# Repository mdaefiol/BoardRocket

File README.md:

# BoardRocket
Placa utilizada como computador de bordo para foguetes experimentais (REV-A 06/06/23).

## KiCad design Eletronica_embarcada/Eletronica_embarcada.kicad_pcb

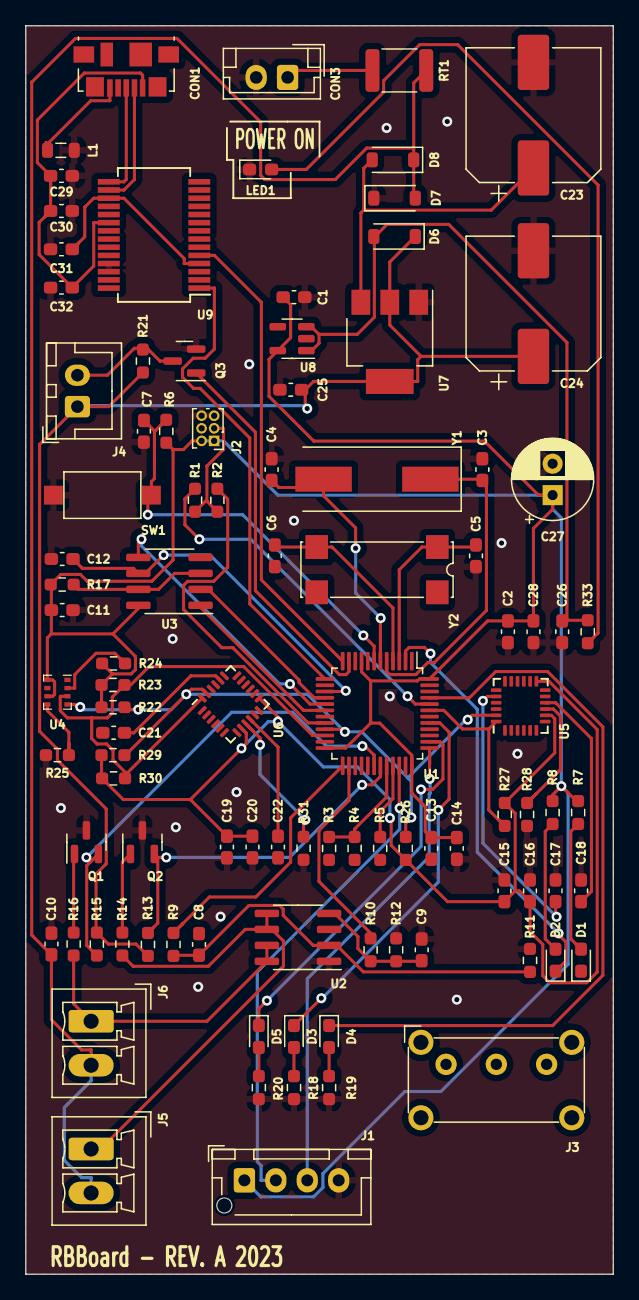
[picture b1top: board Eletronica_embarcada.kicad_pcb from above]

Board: 2 copper layers, 46.7 x 99.3 mm, 98 parts (0 on the bottom side), 65 nets.

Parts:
C1, C2, C7, C8, C9, C25: 100n; C_0603_1608Metric_Pad1.08x0.95mm_HandSolder
C3, C4, C5, C6: 20p; C_0603_1608Metric_Pad1.08x0.95mm_HandSolder
C10, C14: 1u; C_0603_1608Metric_Pad1.08x0.95mm_HandSolder
C11, C26, C28, C32: 100nF; C_0603_1608Metric_Pad1.08x0.95mm_HandSolder
C12: 47pF; C_0603_1608Metric_Pad1.08x0.95mm_HandSolder
C13: 0.1u; C_0603_1608Metric_Pad1.08x0.95mm_HandSolder
C15, C18, C19, C22: 0.1uF; C_0603_1608Metric_Pad1.08x0.95mm_HandSolder
C16, C20: 0.01uF; C_0603_1608Metric_Pad1.08x0.95mm_HandSolder
C17, C21: 2200pF; C_0603_1608Metric_Pad1.08x0.95mm_HandSolder
C23: 470u, 16V; CP_Elec_10x10.5
C24: 1000u,16V; CP_Elec_10x10.5
C27: 220uFx16V; CP_Radial_D6.3mm_P2.50mm
C29: 10nF; C_0603_1608Metric_Pad1.08x0.95mm_HandSolder
C30: 4,7uF; C_0603_1608Metric_Pad1.08x0.95mm_HandSolder
C31: 1uF; C_0603_1608Metric_Pad1.08x0.95mm_HandSolder
CON1: USB_B; USB_Micro-B_Molex_47346-0001
CON3: Bateria min 7V; JST_EH_B2B-EH-A_1x02_P2.50mm_Vertical
D1, D2, D3, D4, D5: LED; LED_0603_1608Metric_Pad1.05x0.95mm_HandSolder
D6, D8: D; D_SOD-123
D7: DSS14U; D_SOD-123
J1: OUT_Bluepill; JST_XH_B4B-XH-AM_1x04_P2.50mm_Vertical
J2: BOOT_JUMPER; PinHeader_2x03_P1.00mm_Vertical
J3: Switch; SW_E-Switch_EG1224_SPDT_Angled
J4: BUZZER; JST_XH_B2B-XH-A_1x02_P2.50mm_Vertical
J5, J6: Screw_Terminal; PhoenixContact_MCV_1,5_2-G-3.5_1x02_P3.50mm_Vertical
L1: BBPY0020; L_0805_2012Metric
LED1: Power ON; LED_0603_1608Metric_Pad1.05x0.95mm_HandSolder
Q1, Q2: MMBT6427-F; SOT-23
Q3: BC817; SOT-23
R1, R2: 100K; R_0603_1608Metric_Pad0.98x0.95mm_HandSolder
R3, R26, R27, R28, R29, R30, R31: 4.7k; R_0603_1608Metric_Pad0.98x0.95mm_HandSolder
R4, R5: 20R; R_0603_1608Metric_Pad0.98x0.95mm_HandSolder
R6, R11, R12, R13, R15: 10k; R_0603_1608Metric_Pad0.98x0.95mm_HandSolder
R7: 510R; R_0603_1608Metric_Pad0.98x0.95mm_HandSolder
R8: 510; R_0603_1608Metric_Pad0.98x0.95mm_HandSolder
R9, R10: 1.5K; R_0603_1608Metric_Pad0.98x0.95mm_HandSolder
R14, R16: 1M; R_0603_1608Metric_Pad0.98x0.95mm_HandSolder
R17: 22k; R_0603_1608Metric_Pad0.98x0.95mm_HandSolder
R18, R19, R20: 330; R_0603_1608Metric_Pad0.98x0.95mm_HandSolder
R21: 1,5k; R_0603_1608Metric_Pad0.98x0.95mm_HandSolder
R22, R23, R24, R25: 10K; R_0603_1608Metric_Pad0.98x0.95mm_HandSolder
R33: 470R; R_0603_1608Metric_Pad0.98x0.95mm_HandSolder
RT1: 300mA - 304N; R_1812_4532Metric
SW1: SW_Push; SW_SPST_CK_RS282G05A3
U1: STM32F103CBT6; LQFP-48_7x7mm_P0.5mm
U2: IRF7101; SOIC-8_3.9x4.9mm_P1.27mm
U3: MB85RS256B; SOIC-8_3.9x4.9mm_P1.27mm
U4: BMP280; Bosch_LGA-8_2x2.5mm_P0.65mm_ClockwisePinNumbering
U5, U6: MPU-6050; InvenSense_QFN-24_4x4mm_P0.5mm
U7: NCP1117-5.0_SOT223; SOT-223-3_TabPin2
U8: TPS7A0533PDBV; SOT-23-5
U9: FT232RL; SSOP-28_5.3x10.2mm_P0.65mm
Y1: 8M; Crystal_SMD_HC49-SD
Y2: 32k; Crystal_SMD_SeikoEpson_MA406-4Pin_11.7x4.0mm

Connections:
0: C1.2, C2.2, C3.2, C4.2, C5.2, C6.2, C7.2, C8.2, C9.2, C10.2, C11.2, C12.2, C13.2, C14.2, C15.2, C16.2, C17.2, C18.2, C19.2, C20.2, C21.2, C22.2, C23.2, C24.2, C25.2, C26.2, C27.2, C28.2, C29.2, C30.2, C31.2, C32.2, CON1.4 (GND), CON3.2 (-), D7.1 (K), J1.4, J2.5, J2.6, L1.1, LED1.1 (K), Q1.3 (E), Q2.3 (E), Q3.2 (E), R11.2, R12.2, R18.1, R19.1, R20.1, R25.2, R28.2, R31.2, SW1.2, U1.8 (VSSA), U1.23 (VSS), U1.35 (VSS), U1.47 (VSS), U2.1 (S1), U2.3 (S2), U3.4 (VSS), U4.1 (GND), U4.7 (GND), U5.1 (CLKIN), U5.11 (FSYNC), U5.18 (GND), U6.1 (CLKIN), U6.11 (FSYNC), U6.18 (GND), U7.1 (GND), U8.2 (GND), U9.7 (GND), U9.18 (GND), U9.21 (GND), U9.25 (AGND), U9.26 (TEST)
+3.3V: C15.1, C16.1, C19.1, C20.1, R26.1, R27.1, R29.1, R30.1, U5.8 (VDDIO), U5.13 (VDD), U6.8 (VDDIO), U6.13 (VDD)
+5V: C24.1, C25.1, D6.1 (K), J4.1, R13.1, R15.2, R21.2, U7.2 (VO)
ACCEL1_SDA: R27.2, U1.43 (PB7), U5.24 (SDA)
ACCEL2_SCL: R22.2, R26.2, R29.2, U1.21 (PB10), U4.4 (SCK), U5.23 (SCL), U6.23 (SCL)
ACCEL2_SDA: R23.2, R30.2, U1.22 (PB11), U4.3 (SDI), U6.24 (SDA)
B12_MEM_CS: U1.18 (PB0), U3.1 (*S)
B13_MEM_SCK: C12.1, U1.15 (PA5), U3.6 (C)
B14_MEM_SO: U1.16 (PA6), U3.2 (Q)
B15_MEM_SI: U1.17 (PA7), U3.5 (D)
BOOT0: J2.3, R1.1, R2.1
C13: D2.1 (K), U1.2 (PC13)
IN1: Q1.2 (C), R15.1, U1.30 (PA9)
IN2: Q2.2 (C), R13.2, U1.31 (PA10)
LED_GREEN: D3.1 (K), U1.41 (PB5)
LED_RED: D4.1 (K), U1.45 (PB8)
LED_YELLOW: D5.1 (K), U1.38 (PA15)
unnamed: CON1.3 (D+), U9.15 (USBD+)
unnamed: CON1.2 (D-), U9.16 (USBD-)
unnamed: CON1.5 (Shield), L1.2
unnamed: CON3.1 (+), RT1.1
unnamed: D1.2 (A), R7.2
unnamed: D2.2 (A), R8.2
unnamed: D3.2 (A), R18.2
unnamed: D4.2 (A), R19.2
unnamed: D5.2 (A), R20.2
unnamed: C26.1, D6.2 (A), R33.1, U8.1 (IN), U8.3 (EN)
unnamed: C23.1, D8.2 (A), U7.3 (VI)
unnamed: J4.2, Q3.3 (C), R21.1
unnamed: J5.1, R14.2, U2.5 (D2), U2.6 (D2)
unnamed: J6.1, R16.2, U2.7 (D1), U2.8 (D1)
unnamed: LED1.2 (A), R33.2
unnamed: Q1.1 (B), R16.1
unnamed: Q2.1 (B), R14.1
unnamed: R1.2, U1.44 (BOOT0)
unnamed: R3.2, R4.1, U1.32 (PA11)
unnamed: R5.1, U1.33 (PA12)
unnamed: R2.2, U1.20 (PB2)
unnamed: C5.1, U1.3 (PC14), Y2.1
unnamed: C6.1, U1.4 (PC15), Y2.2
unnamed: C3.1, U1.5 (PD0), Y1.1
unnamed: C4.1, U1.6 (PD1), Y1.2
unnamed: C8.1, R9.2, R11.1, U2.2 (G1)
unnamed: C9.1, R10.2, R12.1, U2.4 (G2)
unnamed: R17.2, U3.3 (*W), U3.7 (*HOLD)
unnamed: R24.2, U4.2 (CSB)
unnamed: R25.1, U4.5 (SDO)
unnamed: R28.1, U5.9 (AD0)
unnamed: C17.1, U5.20 (CPOUT)
unnamed: C18.1, U5.10 (REGOUT)
unnamed: R31.1, U6.9 (AD0)
unnamed: C21.1, U6.20 (CPOUT)
unnamed: C22.1, U6.10 (REGOUT)
unnamed: C31.1, U9.4 (VCCIO), U9.17 (3V3OUT)
OUT1: R9.1, U1.25 (PB12)
OUT2: R10.1, U1.26 (PB13)
Pin_BUZZER: Q3.1 (B), U1.11 (PA1)
RXA: U1.12 (PA2), U9.5 (RXD)
Reset: C7.1, R6.2, SW1.1, U1.7 (NRST)
SWCLK: J1.3, U1.37 (PA14)
SWDIO: J1.2, U1.34 (PA13)
TXA: U1.13 (PA3), U9.1 (TXD)
VBAT: C10.1, D7.2 (A), D8.1 (K), J5.2, J6.2, RT1.2
VDDIO: C1.1, C2.1, C11.1, C13.1, C14.1, C27.1, C28.1, J1.1, J2.1, J2.2, R6.1, R7.1, R8.1, R17.1, R22.1, R23.1, R24.1, U1.9 (VDDA), U1.24 (VDD), U1.36 (VDD), U1.48 (VDD), U3.8 (VDD), U4.6 (VDDIO), U4.8 (VDD), U8.5 (OUT)
VDD_FTD: C29.1, C30.1, C32.1, CON1.1 (VBUS), U9.20 (VCC)

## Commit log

2023-05-22 esquemático revisado.
    necessário adicionar circuito segundo acelerômetro.
2023-05-24 finalizado.
